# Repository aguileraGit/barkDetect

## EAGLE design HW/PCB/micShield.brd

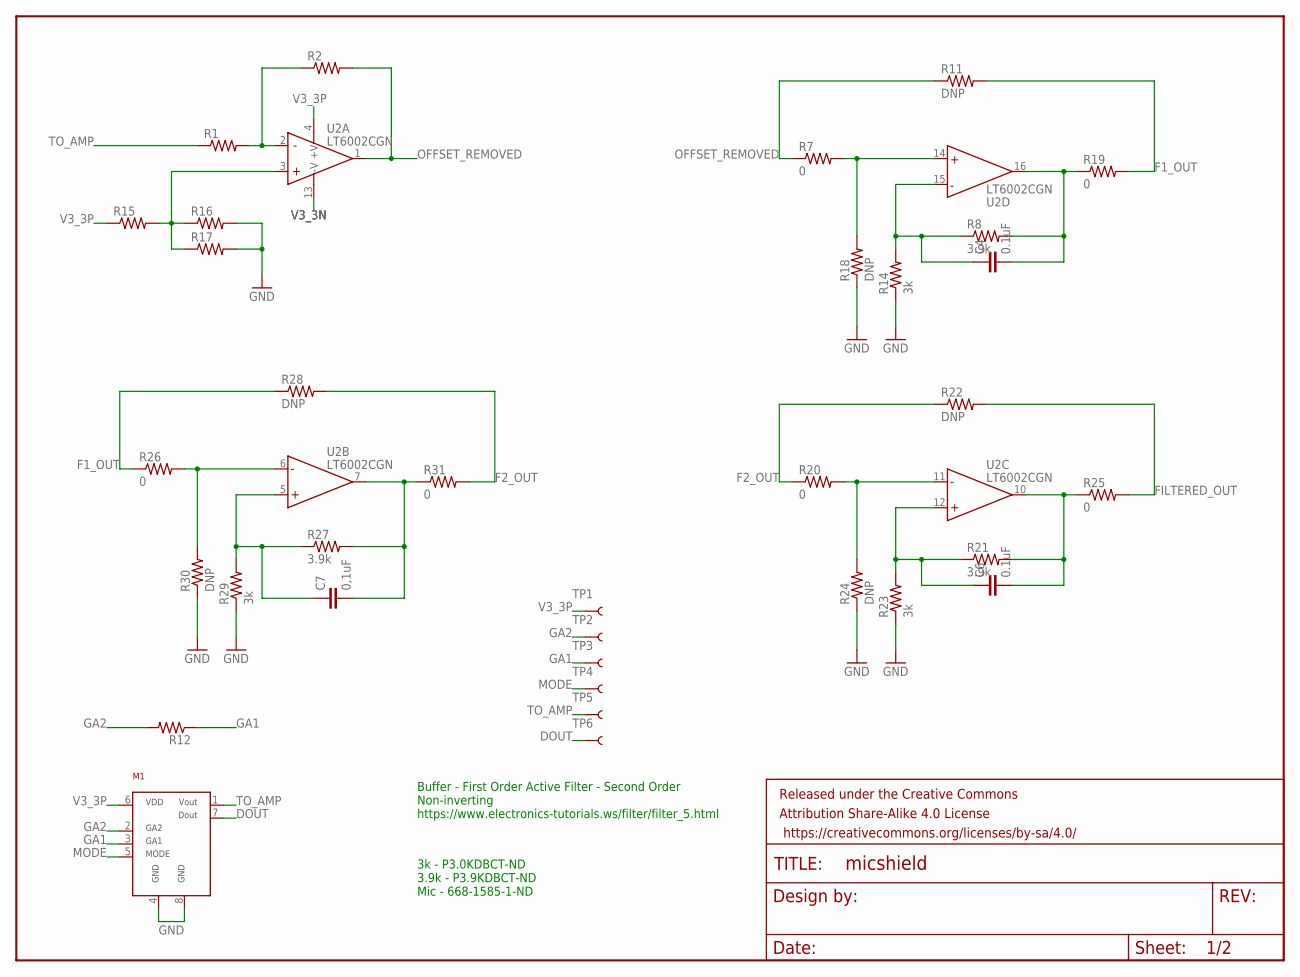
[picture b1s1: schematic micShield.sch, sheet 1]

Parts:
C4, C6: 0.1uF; 0402-CAP
C7: 0,1uF; 0402-CAP
FRAME1: FRAME-LETTER; CREATIVE_COMMONS
M1: PMM-3738-VM1010-R
R1, R2, R12, R15, R16, R17: RESISTOR0402; 0402-RES
R7, R19, R20, R25, R26, R31: 0; 0402-RES
R8, R21, R27: 3.9k; 0402-RES
R11, R18, R22, R24, R28, R30: DNP; 0402-RES
R14, R23, R29: 3k; 0402-RES
TP1, TP2, TP3, TP4, TP5, TP6: TEST-POINT3; PAD.03X.03
U2: LT6002CGN; SSOP-16_GN

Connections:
DOUT: M1.7, TP6.P$1; also elsewhere on the board
F1_OUT: R11.2, R19.2, R26.1, R28.1
F2_OUT: R20.1, R22.1, R28.2, R31.2
FILTERED_OUT: R22.2, R25.2; also elsewhere on the board
GA1: M1.3, R12.1, TP3.P$1
GA2: M1.2, R12.2, TP2.P$1
GND: M1.4, M1.8, R14.1, R16.2, R17.2, R18.1, R23.1, R24.1, R29.1, R30.1; also elsewhere on the board
MODE: M1.5, TP4.P$1; also elsewhere on the board
unnamed: R1.2, R2.1, U2.2 (-IN)
unnamed: R15.2, R16.1, R17.1, U2.3 (+IN)
unnamed: C4.1, R8.1, R14.2, U2.15 (-IN)
unnamed: R7.2, R18.2, U2.14 (+IN)
unnamed: C4.2, R8.2, R19.1, U2.16 (OUT)
unnamed: R20.2, R24.2, U2.11 (-IN)
unnamed: C6.1, R21.1, R23.2, U2.12 (+IN)
unnamed: C6.2, R21.2, R25.1, U2.10 (OUT)
unnamed: R26.2, R30.2, U2.6 (-IN)
unnamed: C7.1, R27.1, R29.2, U2.5 (+IN)
unnamed: C7.2, R27.2, R31.1, U2.7 (OUT)
OFFSET_REMOVED: R2.2, R7.1, R11.1, U2.1 (OUT)
TO_AMP: M1.1, R1.1, TP5.P$1
V3_3N: U2.13 (-V); also elsewhere on the board
V3_3P: M1.6, R15.1, TP1.P$1, U2.4 (+V); also elsewhere on the board

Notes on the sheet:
Buffer - First Order Active Filter - Second Order Non-inverting https://www.electronics-tutorials.ws/filter/filter_5.html
3k - P3.0KDBCT-ND 3.9k - P3.9KDBCT-ND Mic - 668-1585-1-ND

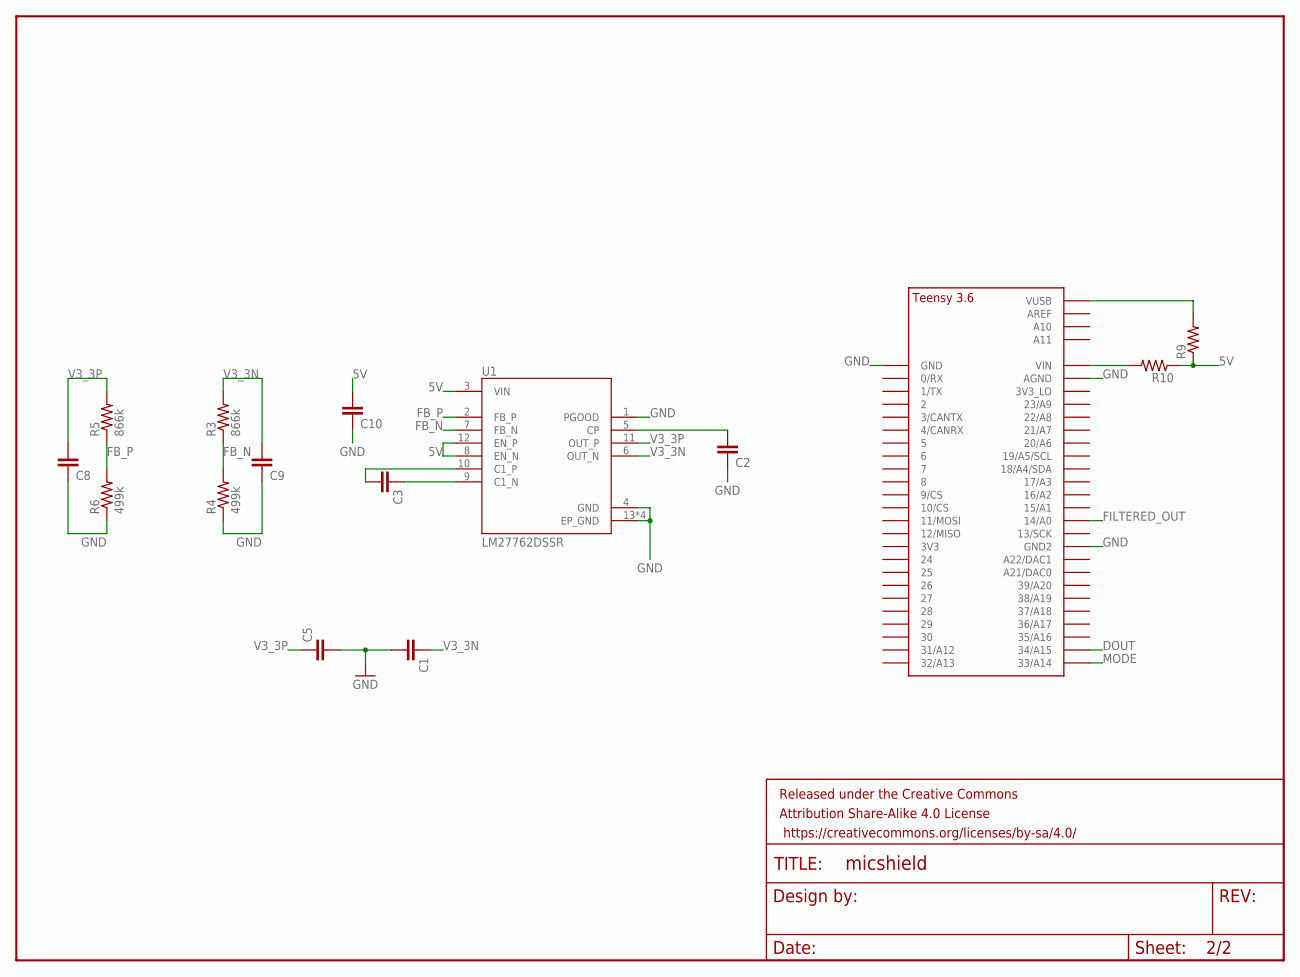
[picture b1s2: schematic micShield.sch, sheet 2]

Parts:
C1, C2, C5, C8, C9, C10: CAP0603-CAP; 0603-CAP
C3: CAP0402-CAP; 0402-CAP
FRAME2: FRAME-LETTER; CREATIVE_COMMONS
R3, R5: 866k; 0402-RES
R4, R6: 499k; 0402-RES
R9, R10: RESISTOR0402; 0402-RES
U1: LM27762DSSR; VREG_LM27762DSSR
U$1: TEENSY_3.5/3.6_BASIC

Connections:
5V: C10.2, R9.1, R10.1, U1.3 (VIN), U1.8 (EN_N), U1.12 (EN_P)
DOUT: U$1.34/A15; also elsewhere on the board
FB_N: R3.1, R4.2, U1.7 (FB_N)
FB_P: R5.1, R6.2, U1.2 (FB_P)
FILTERED_OUT: U$1.14/A0; also elsewhere on the board
GND: C1.2, C2.1, C5.2, C8.1, C9.1, C10.1, R4.1, R6.1, U1.1 (PGOOD), U1.4 (GND), U1.13 (EP_GND), U1.13.1 (EP_GND), U1.13.2 (EP_GND), U1.13.3 (EP_GND), U$1.AGND, U$1.GND, U$1.GND2; also elsewhere on the board
MODE: U$1.33/A14; also elsewhere on the board
unnamed: C2.2, U1.5 (CP)
unnamed: C3.1, U1.9 (C1_N)
unnamed: C3.2, U1.10 (C1_P)
unnamed: R9.2, U$1.VUSB
unnamed: R10.2, U$1.VIN
V3_3N: C1.1, C9.2, R3.2, U1.6 (OUT_N); also elsewhere on the board
V3_3P: C5.1, C8.2, R5.2, U1.11 (OUT_P); also elsewhere on the board

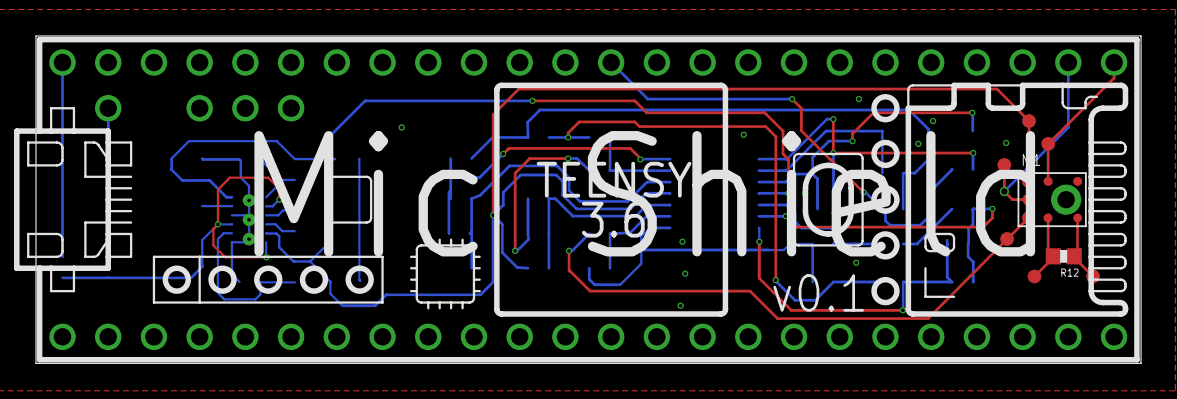
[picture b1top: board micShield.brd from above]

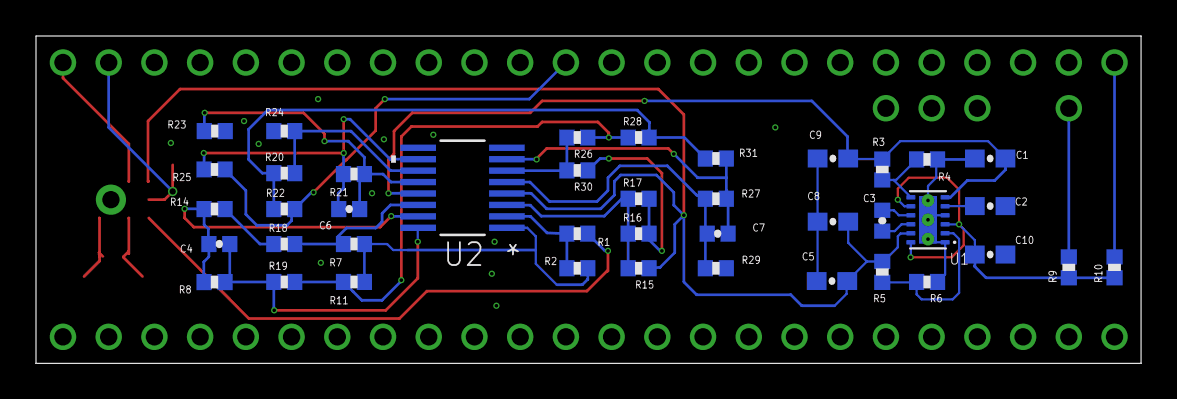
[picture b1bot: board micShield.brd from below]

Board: 2 copper layers, 61.4 x 18.2 mm, 52 parts (42 on the bottom side), 31 nets.

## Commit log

2018-05-11 Init commit
2018-05-11 Create fftUpdates
    Removed scikit. Probably doing FFT (adjusted and reduced length)
2018-05-14 Moving to new system. Need to figure out how to finish saving the JSON.
2018-05-15 Fixed saving to json. Starting working on combining data.
2018-05-15 Added actual code
    Still needs work. Export not written.
2018-05-16 Bug! Data exported from recordAudio just has a single value repeated over and over. Fix it.
2018-05-17 Working.
2018-05-18 Made some updates to be able to export time series data. Code works. But it can't identify samples correctly.
2018-05-21 Added loopPredict I think I went back to FFT for training and prediction
2018-05-22 More updates to loopPredict. Needs to be finished.
2018-05-23 Added loopPredict. Needs be modified to be quicker. Modified tinn.py. Hopefully it doesn't break anything.
2018-05-23 Need to integrate testAudioCaptureStream into loopPredict
2018-05-24 Works(ish). But it's slow. Need to implement call backs.
2018-05-25 Updated loopPredict. Added testAudioCaptureStream. Can be removed.
2018-05-28 Working better. Probably need more samples.
2018-05-29 Working. Need to add more woofs for training.
2018-05-30 Added more training data. Adjusted Training. Deleted time series data. Better at detecting woofs. Should look at normalizing data(?)
2018-05-30 Added changes from previous day
2018-05-30 Merged all files Added to do file
2018-06-04 Adding PCB
2018-06-06 Added Mic Library and updates to PCB.
2018-06-12 Adding libs. Working on analog front end.
2018-06-15 More updates to the PCB. Added +/-3V
2018-06-18 Routing updates.
2018-06-20 Schematics and Layout updates.
2018-06-21 More updates to schematics and layout.
2018-06-27 Woohoo. Version 0.1 ordered.
2018-07-06 Adding layout.
2018-07-10 Adding top layer layout. Adding CAM File.
2018-07-10 Adding Teensy code.
2018-07-10 Quick update before bed.
2018-07-11 Updated code with some hints.
2018-07-12 Updating PDFs
2018-07-12 Updated a bunch of references. Need to figure out the registers.
2018-07-13 Adding audio clips for testing.
2018-07-15 Updated code. Should blink pin 13 @ 4k. Need to test.
2018-07-17 Cleaned up code. Should still blink pin 13 @ 4khz.
2018-07-23 Cleaned up code.
2018-08-10 Updates from lunch time coding
2018-08-14 Update some code.
    Really need to pull this in.
2018-08-15 Adding newline at the end of woofsAndMeows.data. - Not data for training. Added some Arduino test code. - Not reading the SD Card.
2018-08-16 Able to read 51 lines. Not sure what changed.
2018-08-20 Updated code
    Error before parse. Only parsing 0.000 during parse function.
2018-08-21 (Hopefully) Fixed string issue.
    Pretty sure I fixed issue in lineRead function where the line was blank.
2018-08-21 Different error.
    Won't return from function!
2018-08-21 Working
    Able to Load, Train, and Predict using values loaded on SD Card.
2018-08-24 Loading/Saving - Need to test
    Load and Save Tinn NN functions added. Currently locks up device after loading NN.
2018-08-27 Loading error
    Error when loading NN data. (Without loading and training).
    Error if I try and load data twice.
2018-08-28 Updated Arduino code.
    Load/Train/Predict works in that order.
2018-08-28 Adding Tinn.c and Tinn.h
    Adding in required files.
2018-08-29 Still not working
    Loading data. Training data. Saving data. -> All works
    When I try Loading Tinn NN and save again, I get zeroooooo at the end of the file. No idea where they're coming from.
2018-08-30 Better - Able to load Tinn file
    Still can't load Tinn file and Data file to test.
    Change prediction function to allow for prediction of single value?

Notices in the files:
parts and their libraries:
SparkFun-Capacitors: Licensing: Creative Commons ShareAlike 4.0 International - https://creativecommons.org/licenses/by-sa/4.0
SparkFun-Aesthetics: Released under the Creative Commons
SparkFun-Aesthetics: https://creativecommons.org/licenses/by-sa/4.0
